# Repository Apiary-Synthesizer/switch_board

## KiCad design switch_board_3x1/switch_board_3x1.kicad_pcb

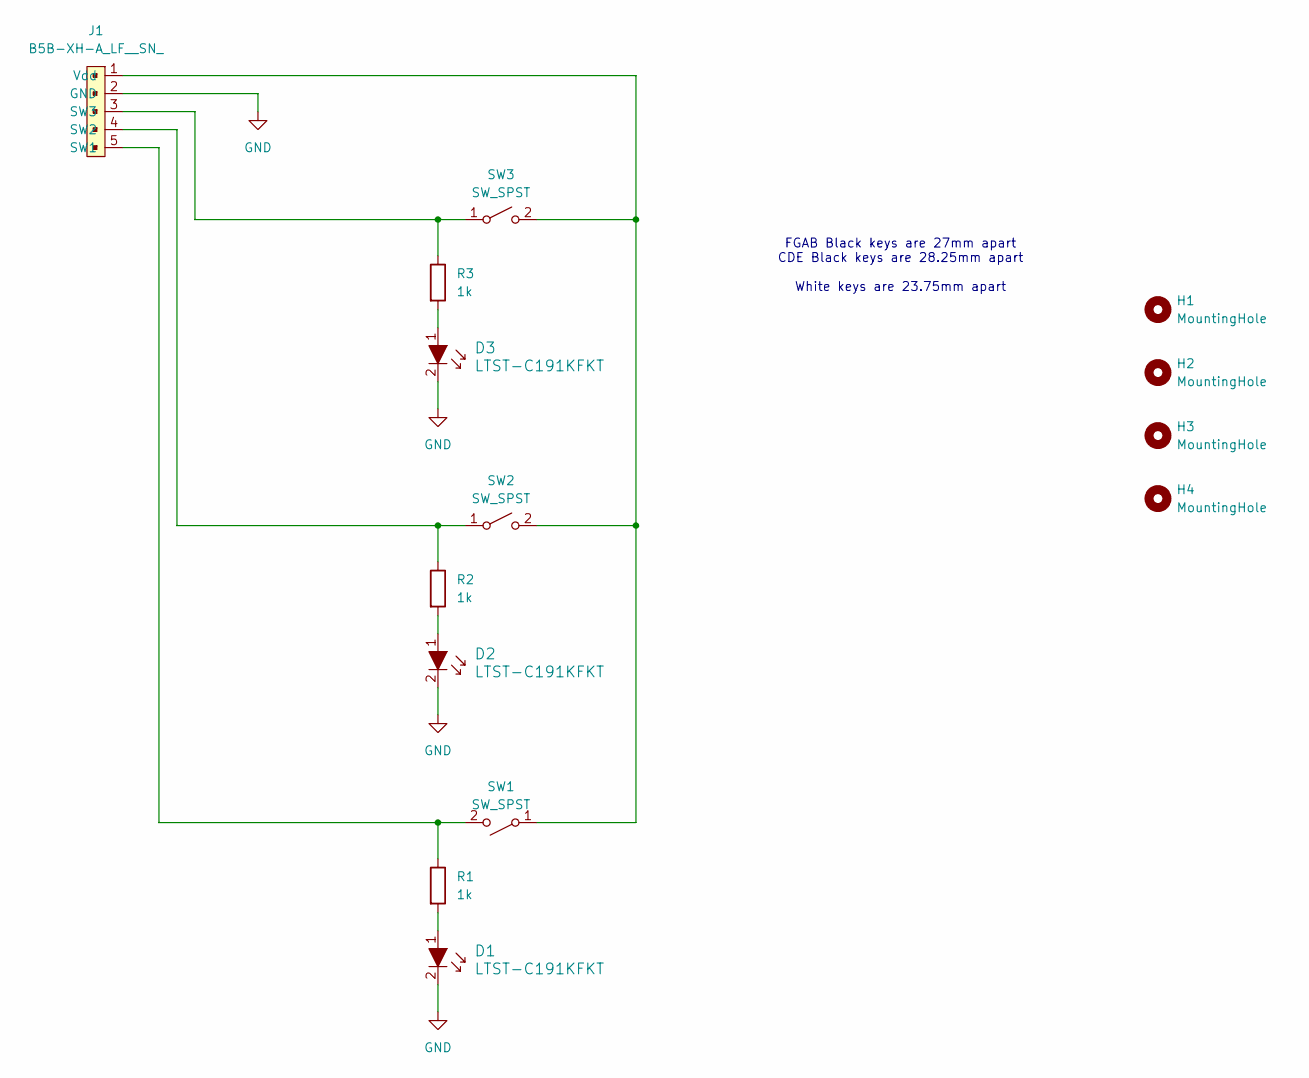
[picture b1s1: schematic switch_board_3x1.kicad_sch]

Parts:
D1, D2, D3: LTST-C191KFKT; LED_0603_1608Metric; MPN LTST-C191KFKT; Digi-Key_PN 160-1445-1-ND
H1, H2, H3, H4: MountingHole; MountingHole_3.7mm
J1: B5B-XH-A_LF__SN_; PinHeader_1x05_P2.54mm_Vertical; MPN B5B-XH-A(LF)(SN); Digi-Key_PN 455-2270-ND
R1, R2, R3: 1k; R_0603_1608Metric
SW1, SW2, SW3: SW_SPST; SW_Cherry_MX_PCB_1.00u_3D_Model

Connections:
GND: D1.2, D2.2, D3.2, J1.2 (GND)
unnamed: D1.1, R1.2
unnamed: D2.1, R2.2
unnamed: D3.1, R3.2
unnamed: J1.5 (SW1), R1.1, SW1.2 (B)
unnamed: J1.4 (SW2), R2.1, SW2.1 (A)
unnamed: J1.3 (SW3), R3.1, SW3.1 (A)
unnamed: J1.1 (Vdd), SW1.1 (A), SW2.2 (B), SW3.2 (B)

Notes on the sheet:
FGAB Black keys are 27mm apart CDE Black keys are 28.25mm apart White keys are 23.75mm apart

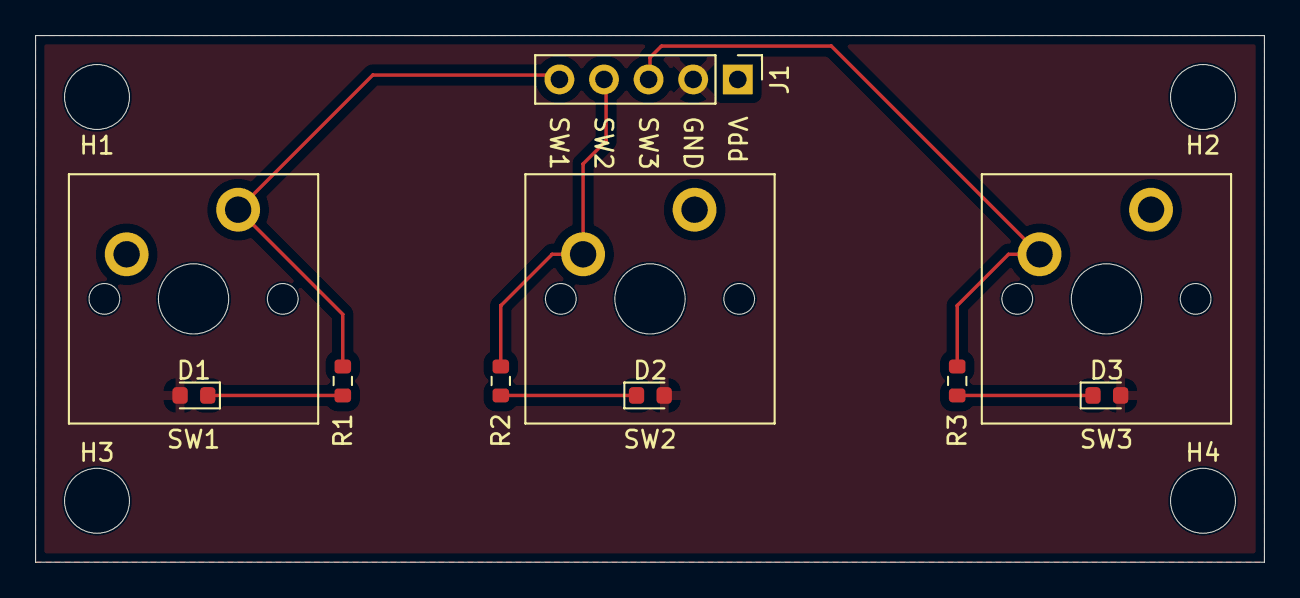
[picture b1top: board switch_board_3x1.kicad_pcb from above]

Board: 2 copper layers, 70.0 x 30.0 mm, 14 parts (0 on the bottom side), 8 nets.

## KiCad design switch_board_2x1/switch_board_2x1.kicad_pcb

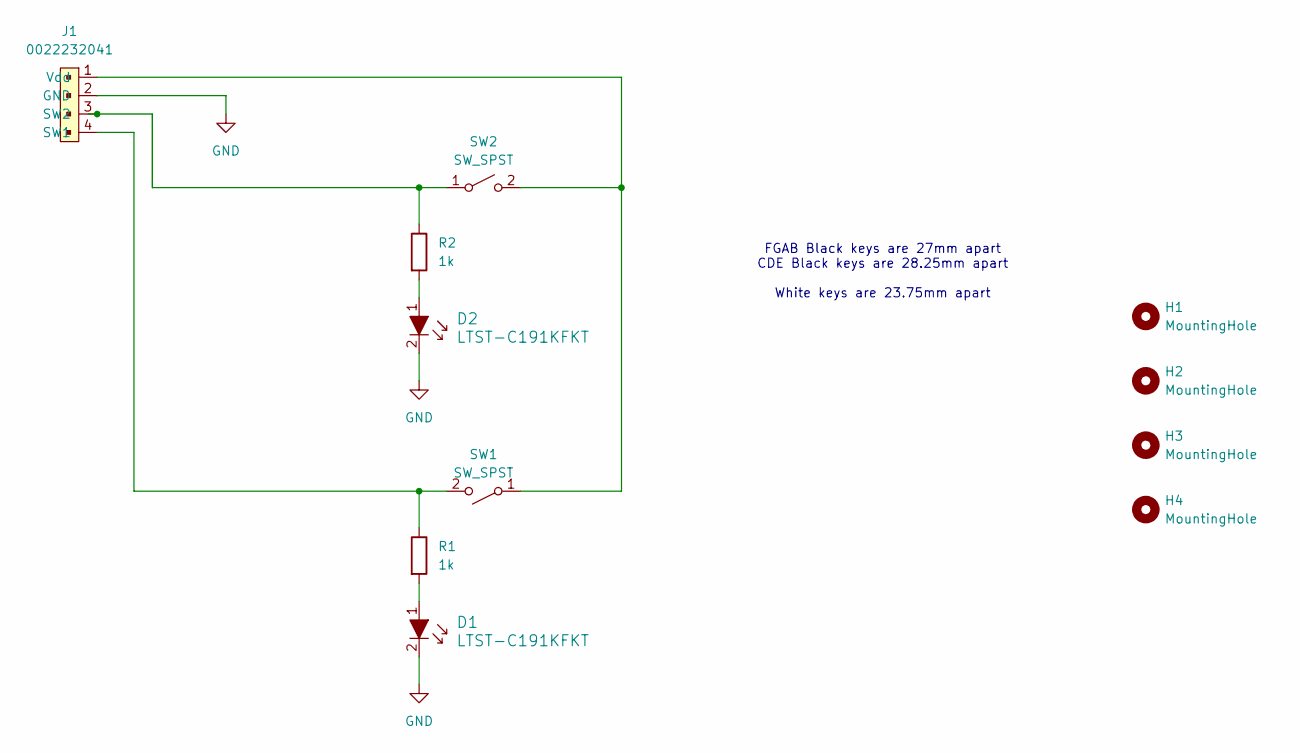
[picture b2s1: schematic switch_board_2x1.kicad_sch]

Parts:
D1, D2: LTST-C191KFKT; LED_0603_1608Metric; MPN LTST-C191KFKT; Digi-Key_PN 160-1445-1-ND
H1, H2, H3, H4: MountingHole; MountingHole_3.7mm
J1: 0022232041; PinHeader_1x04_P2.54mm_Vertical; MPN 0022232041; Digi-Key_PN WM4202-ND
R1, R2: 1k; R_0603_1608Metric
SW1, SW2: SW_SPST; SW_Cherry_MX_PCB_1.00u_3D_Model

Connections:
GND: D1.2, D2.2, J1.2 (GND)
unnamed: D1.1, R1.2
unnamed: D2.1, R2.2
unnamed: J1.4 (SW1), R1.1, SW1.2 (B)
unnamed: J1.3 (SW2), R2.1, SW2.1 (A)
unnamed: J1.1 (Vdd), SW1.1 (A), SW2.2 (B)

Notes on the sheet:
FGAB Black keys are 27mm apart CDE Black keys are 28.25mm apart White keys are 23.75mm apart

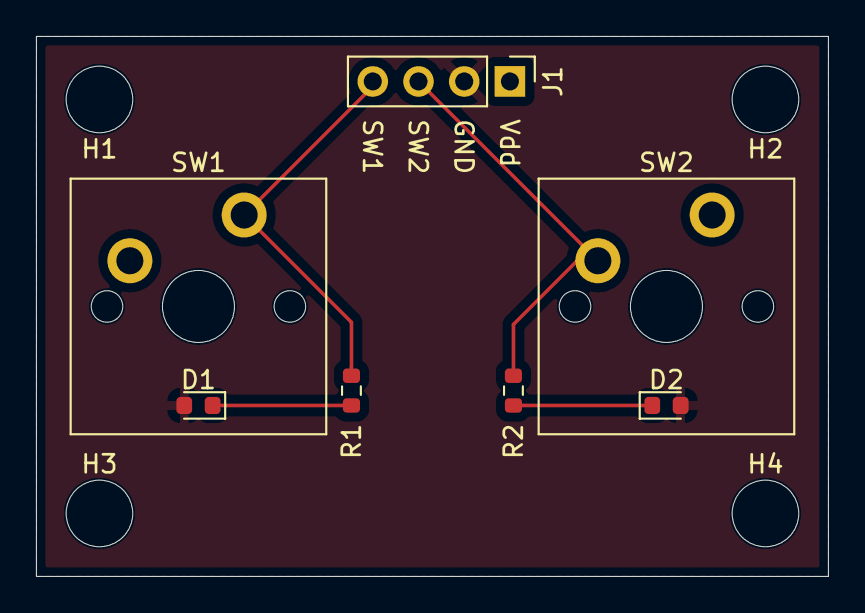
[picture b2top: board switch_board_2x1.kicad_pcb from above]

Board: 2 copper layers, 44.0 x 30.0 mm, 11 parts (0 on the bottom side), 6 nets.

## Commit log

2026-02-02 Set up gitignore and symbol/footprint libraries
2026-02-02 Created initial schematic of 2-switch board with header inputs/outputs
2026-02-03 Created initial version of layout for 2x1 switch board; reorganized repo to house KiCad projects for both the 2x1 and 3x1 boards
2026-02-04 Revised layout for 2x1 switch board using GND and power pours; added in 3D models for switches and other components
2026-02-05 Fixing DRC violations/issues for 2x1 board
2026-02-05 Created initial version of 3x1 board (schematic & layout) based on schematic and layout dimensions from 2x1 board
2026-02-06 Updated header footprints to be based on KiCad default library; cleaned up silkscreen and re-checked DRC
2026-02-07 Created custom honeycomb silkscreen graphics for the boards using Figma (very importantgit status)
